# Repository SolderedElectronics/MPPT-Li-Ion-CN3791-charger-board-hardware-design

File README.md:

# MPPT Li-Ion CN3791 charger board Hardware Design

## About the Product

|  |
| :----------------------------------------------------------: |
| [Buy MPPT Li-Ion CN3791 charger board](https://www.solde.red/333136) |

Introducing our new MPPT Li-Ion charger, your all-in-one solution for efficient and reliable battery charging using solar energy! Whether you’re a hobbyist tinkering with electronics or a professional in need of a compact charging solution, this board will make things easier.

On board is the CN3791 which provides sophisticated charging algorithms tailored to Li-Ion batteries, ensuring precise control over the charging process for maximum efficiency and safety. Next to it, there are quick terminals with springs on the board for an even simpler and faster connection of the solar panel and battery. There is also a JST connector for connecting all li-ion batteries from our offer.

---

## Repository Contents

This repository contains all design files for MPPT Li-Ion CN3791 charger board, organized as follows:

- **`CAD` folder**: Contains KiCAD design files, including:
  - Schematics
  - PCB layout
  - Panel PCB layout
  - Source 3D files in Fusion360, if any
  - All files are sorted by version with a detailed change log.
- **`OUTPUTS` folder**: Includes all production-ready files, such as:
  - Bill of Materials (BOM) and interactive BOM (iBOM)
  - PDF versions of schematics
  - 3D `.step` file of the board
  - 3D-printable models
  - Gerber files for PCB manufacturing
  - Image of the pinout of the board
  - Product image
  - Compliance, legal and generic sales documents

Refer to the `Change Log` in the CAD folder for details about updates between versions.

---

## Learn More About the Product

Beyond the repository, explore the following resources:

### Soldered Verify

The **Soldered Verify** system ensures every board you purchase from Soldered is fully functional. It also provides access to exclusive test data for your product. To get started, find the unique Soldered Verify ID on your product's packaging and enter the ID on the [Soldered Verify page](https://soldered.com/verify/) to access test results and additional product details.

### Soldered Community

Soldered Community is your go-to place for technical support. Our engineers track and answer all questions posted there, and it’s a great space for the maker community. Get answers to your questions and solutions for your challenges at [Soldered Community](https://soldered.com/community).

### solde.red

solde.red is an ultimate URL shortener and information hub. Access it by typing solde.red/ followed by your product SKU, e.g., [solde.red/333000](https://solde.red/333000), to find getting-started guides, datasheets, open-source hardware and software files, certifications, images, pinouts, and more. Read more about the shortener [here](https://solde.red/info/).

---

## Contributing

Contributions are welcome! Here’s how you can get involved:

- Submit pull requests to enhance the design or fix issues.
- Report bugs or problems by opening an issue.

We encourage community collaboration to make this product even better.

---

## About Soldered

[Soldered for Makers](https://soldered.com) specializes in designing and manufacturing electronic products tailored for enthusiasts, ranging from hobbyists to professionals. Our portfolio includes electronic boards, sensors, and actuators that are widely utilized in fields such as microelectronics, mechatronics, robotics, programming, and IoT. Every product we offer is designed in-house and built upon open-source hardware and software platforms. Proudly certified and manufactured within the European Union, our catalog likely includes the product you need for your project.

We complement these products with comprehensive tutorials and manuals, product descriptions, schematics, programming codes, and project examples. Our round-the-clock [customer and technical support](https://soldered.com/community) is available for all our products, irrespective of the sales channel. Soldered’s success and services reflect our maker community’s unwavering [trust](https://www.trustpilot.com/review/soldered.com), for which we are deeply grateful. Join our community and create using Soldered products.

---

## License

All Soldered open-source hardware (OSH) is under The TAPR Open Hardware License. Read more in the LICENSE file located in this repository.

**Disclaimer:**

No warranty - all designs in this repository are distributed in the hope that they will be useful, but without any warranty. They are provided "AS IS", therefore without warranty of any kind, either expressed or implied. The entire quality and performance of what you do with the contents of this repository are your responsibility. In no event Soldered Electronics will be liable for your damages, or losses, including any general, special, incidental, or consequential damage arising out of the use or inability to use the contents of this repository. 

---

## Have fun!

Thank you for your support from your fellow makers at Soldered Electronics.

Happy Making!

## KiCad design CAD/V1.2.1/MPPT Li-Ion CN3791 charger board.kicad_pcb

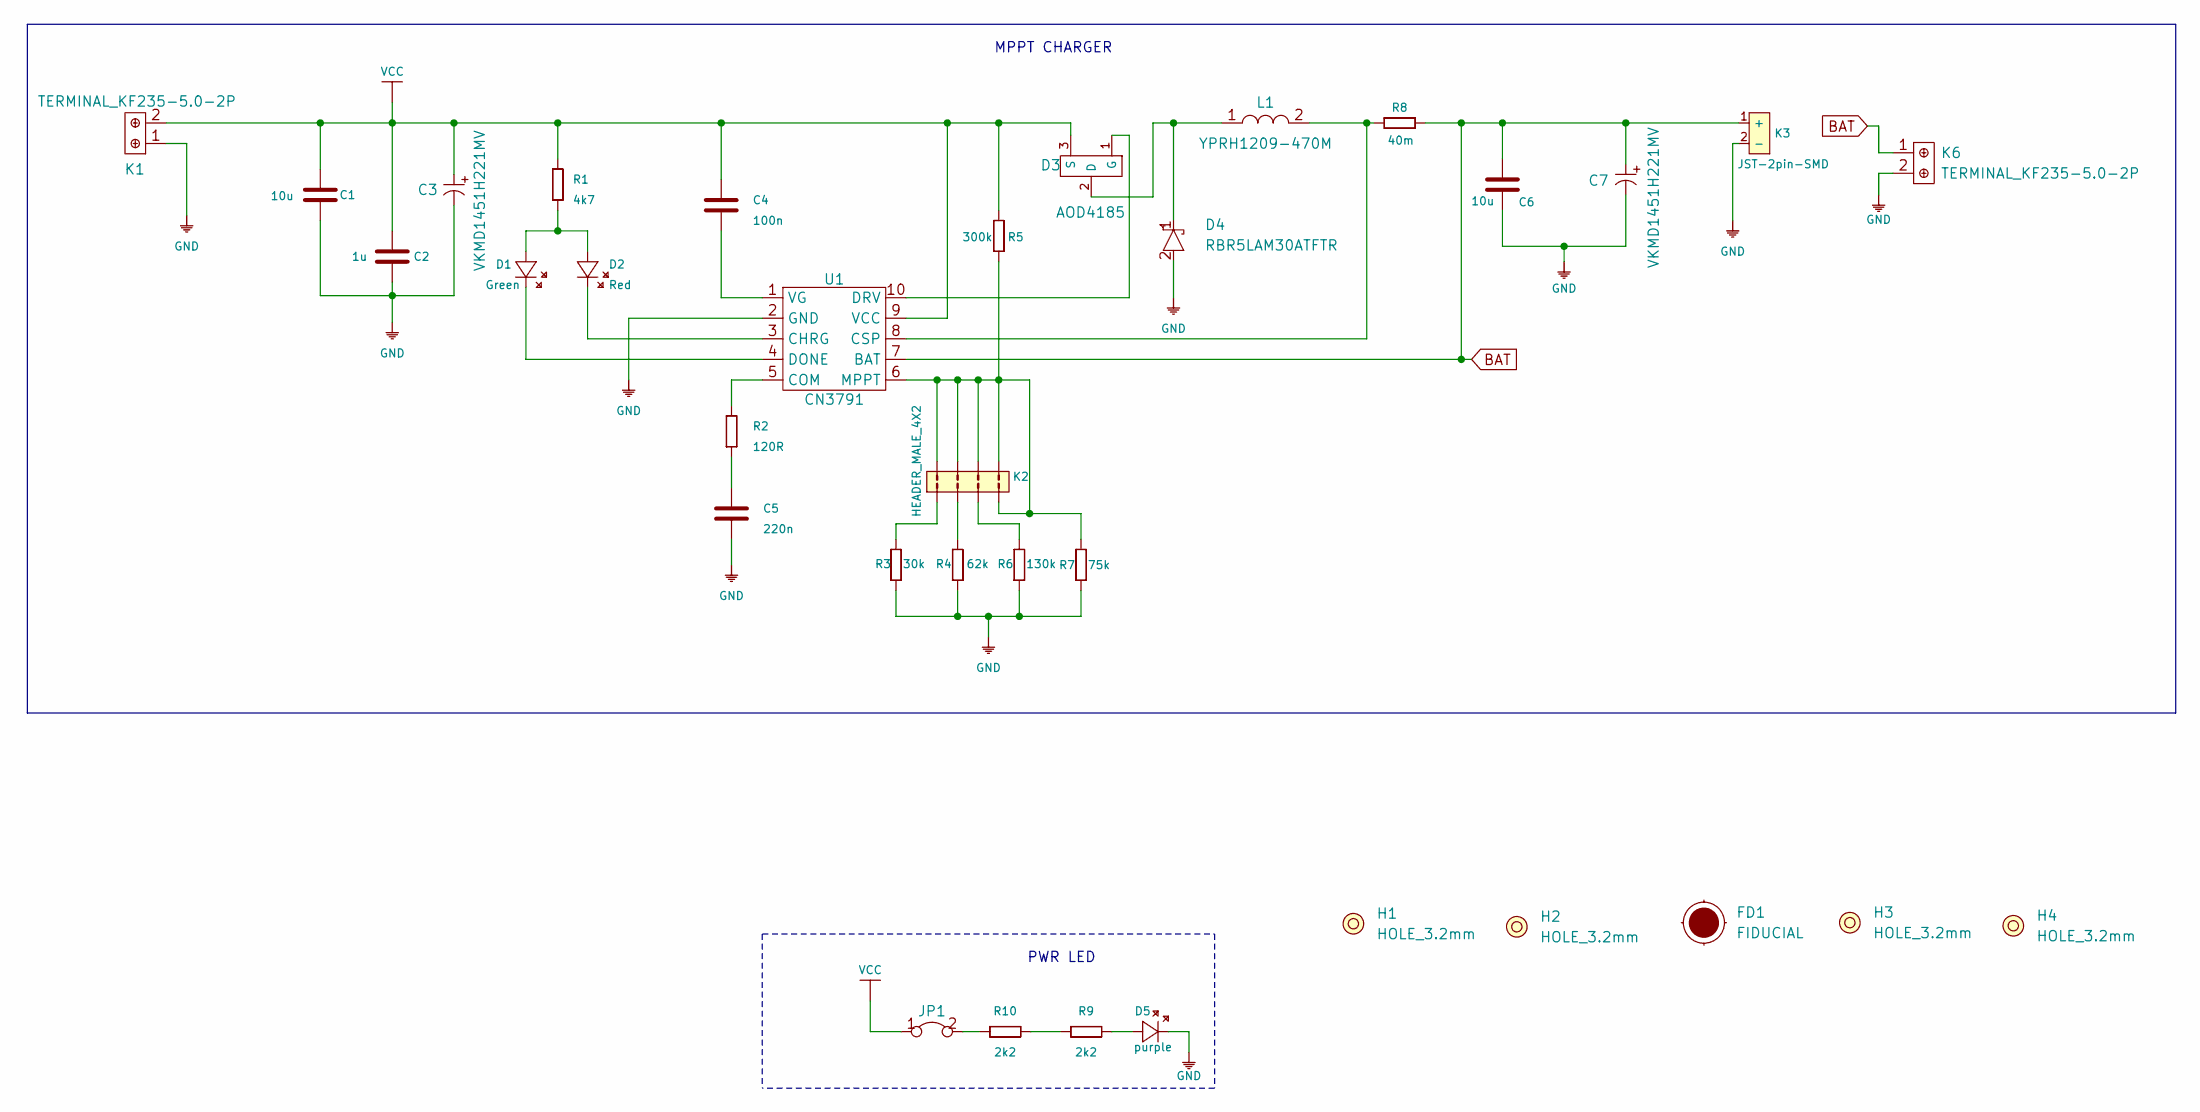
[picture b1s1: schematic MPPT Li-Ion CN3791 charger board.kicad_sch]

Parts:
C1, C6: 10u; 1206C
C2: 1u; 0603C
C3, C7: VKMD1451H221MV; ELECTROLITIC_CAP_8x8x14.5
C4: 100n; 0603C
C5: 220n; 0603C
D1: Green; 0402LED
D2: Red; 0402LED
D3: AOD4185; DPAK
D4: RBR5LAM30ATFTR
D5: purple; 0402LED
FD1: FIDUCIAL; FIDUCIAL_23
H1, H2, H3, H4: HOLE_3.2mm
JP1: SMD-JUMPER-CONNECTED_TRACE_SLODERMASK
K1, K6: TERMINAL_KF235-5.0-2P
K2: HEADER_MALE_4X2
K3: JST-2pin-SMD
L1: YPRH1209-470M
R1: 4k7; 0402R
R2: 120R; 0603R
R3: 30k; 0603R
R4: 62k; 0603R
R5: 300k; 0603R
R6: 130k; 0603R
R7: 75k; 0603R
R8: 40m; 1210R
R9, R10: 2k2; 0402R
U1: CN3791

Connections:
BAT: C6.2, C7.1 (+), K3.1 (+), K6.1, R8.2, U1.7 (BAT)
GND: C1.1, C2.1, C3.2 (-), C5.1, C6.1, C7.2 (-), D4.2 (A), D5.2 (K), K1.1, K3.2 (-), K6.2, R3.1, R4.1, R6.1, R7.1, U1.2 (GND)
unnamed: C4.1, U1.1 (VG)
unnamed: C5.2, R2.1
unnamed: D1.1 (A), D2.1 (A), R1.1
unnamed: D1.2 (K), U1.4 (DONE)
unnamed: D2.2 (K), U1.3 (CHRG)
unnamed: D3.1 (G), U1.10 (DRV)
unnamed: D3.2 (D), D4.1 (C), L1.1
unnamed: D5.1 (A), R9.2
unnamed: JP1.2, R10.1
unnamed: K2.2, R4.2
unnamed: K2.3, R6.2
unnamed: L1.2, R8.1, U1.8 (CSP)
unnamed: R2.2, U1.5 (COM)
unnamed: K2.1, R3.2
unnamed: K2.4, K2.5, K2.6, K2.7, K2.8, R5.1, R7.2, U1.6 (MPPT)
unnamed: R9.1, R10.2
VCC: C1.2, C2.2, C3.1 (+), C4.2, D3.3 (S), JP1.1, K1.2, R1.2, R5.2, U1.9 (VCC)

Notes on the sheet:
MPPT CHARGER
PWR LED

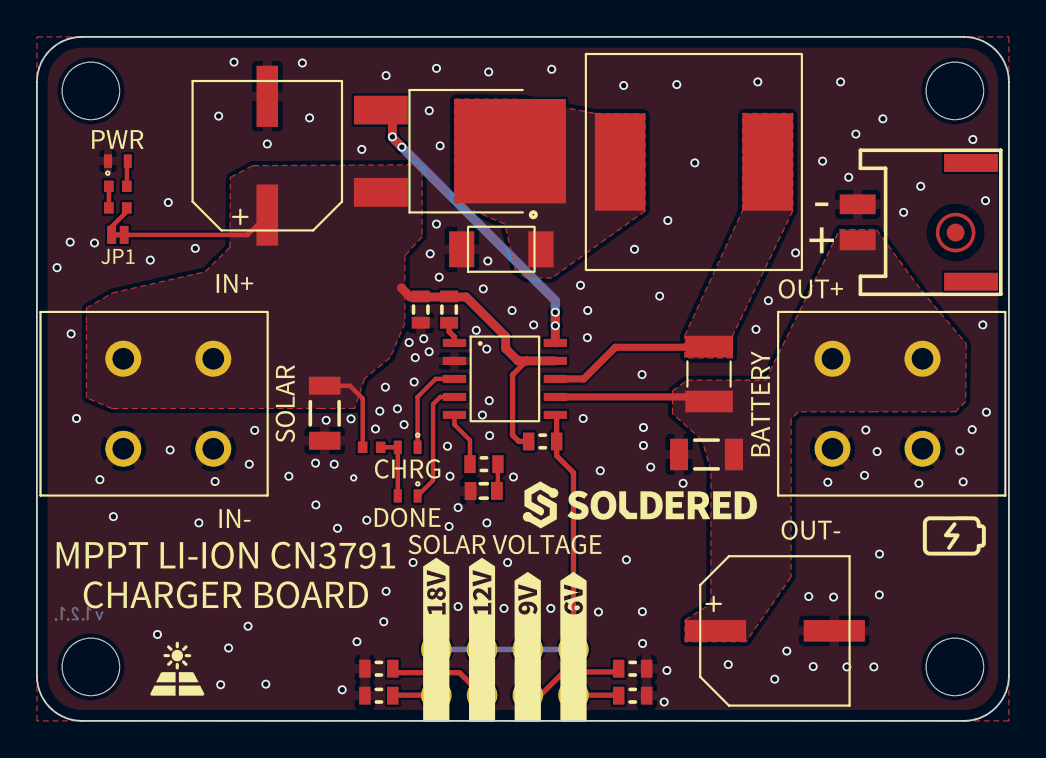
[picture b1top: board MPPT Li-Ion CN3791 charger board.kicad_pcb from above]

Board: 2 copper layers, 54.0 x 38.0 mm, 53 parts (0 on the bottom side), 19 nets.

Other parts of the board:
kibuzzard-63FDC4D6: G***; kibuzzard-63FDC4D6
kibuzzard-63FDC4F1: G***; kibuzzard-63FDC4F1
kibuzzard-63FDC6EA: G***; kibuzzard-63FDC6EA
kibuzzard-63FDC6FB: G***; kibuzzard-63FDC6FB
kibuzzard-63FDC7B8: G***; kibuzzard-63FDC7B8
kibuzzard-63FDC7CB: G***; kibuzzard-63FDC7CB
kibuzzard-63FDC7F0: G***; kibuzzard-63FDC7F0
kibuzzard-63FDC46F: G***; kibuzzard-63FDC46F
kibuzzard-63FDC52C: G***; kibuzzard-63FDC52C
kibuzzard-63FDC496: G***; kibuzzard-63FDC496
kibuzzard-63FDC548: G***; kibuzzard-63FDC548
kibuzzard-63FDC760: G***; kibuzzard-63FDC760
kibuzzard-63FDC769: G***; kibuzzard-63FDC769
kibuzzard-63FDC797: G***; kibuzzard-63FDC797
kibuzzard-65F310BD: G***; kibuzzard-65F310BD
kibuzzard-65F312C9: G***; kibuzzard-65F312C9
kibuzzard-65F312DB: G***; kibuzzard-65F312DB
kibuzzard-65F3056F: G***; kibuzzard-65F3056F
kibuzzard-65F31058: G***; kibuzzard-65F31058

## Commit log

2022-08-06 Updating open source files.
